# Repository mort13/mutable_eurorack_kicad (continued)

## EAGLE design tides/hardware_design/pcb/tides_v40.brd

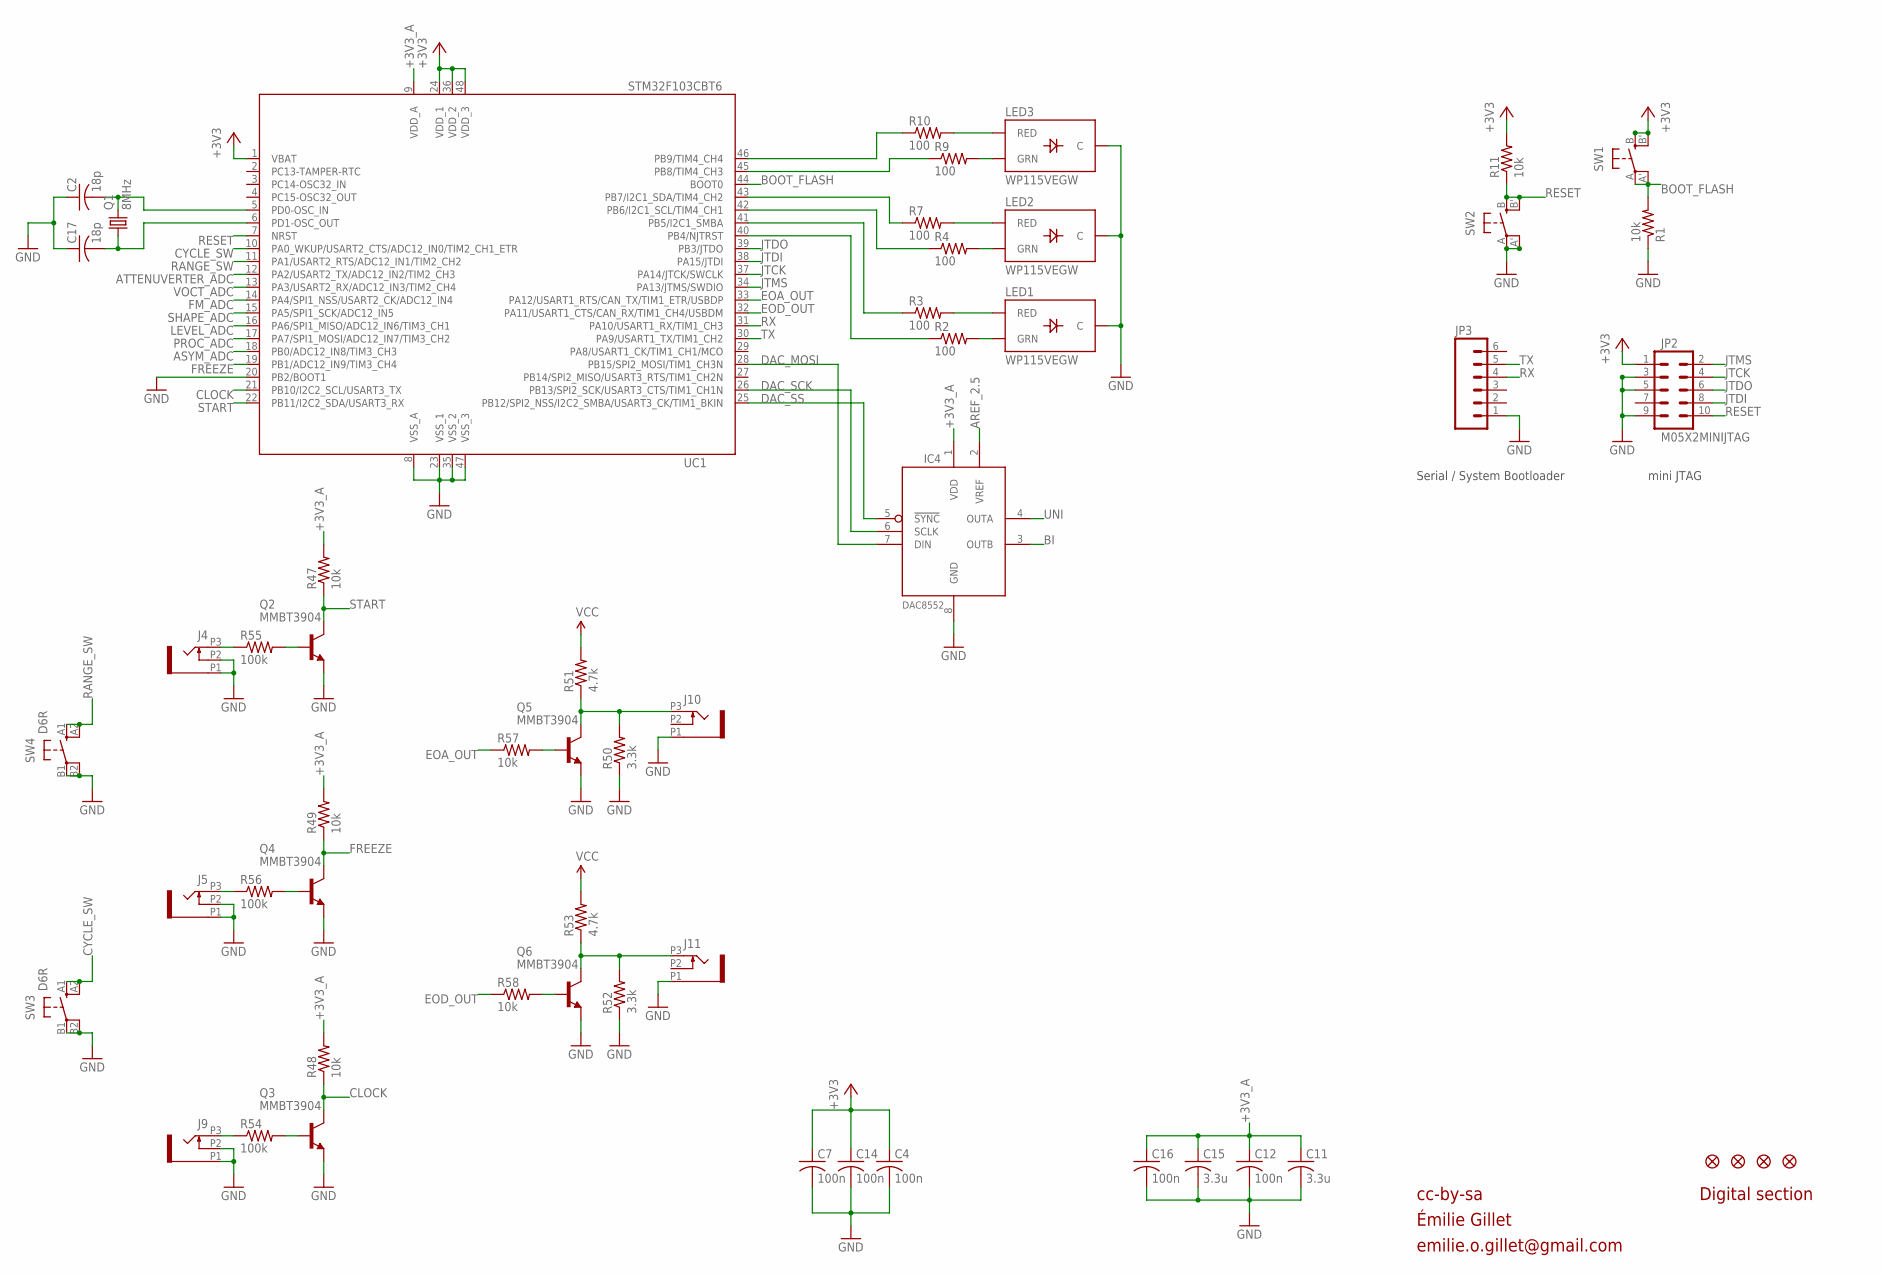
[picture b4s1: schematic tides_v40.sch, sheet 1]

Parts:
C2, C17: 18p; C0603
C4, C7, C12, C14, C16: 100n; C0603
C11, C15: 3.3u; C0603
IC4: DAC8552; MSOP-8
J4, J5, J9, J10, J11: PJ301_THONKICONN6; WQP_PJ_301M6
JP2: M05X2MINIJTAG; 2X5-1.27
JP3: M06SIP; 1X06
JP4, JP5, JP6, JP7: FIDUCIAL1X2; FIDUCIAL-1X2
LED1, LED2, LED3: WP115VEGW; LED-BICOLOR-THROUGHHOLE
Q1: 8MHz; HC49UP
Q2, Q3, Q4, Q5, Q6: MMBT3904; SOT23-BEC
R1, R11, R47, R48, R49, R57, R58: 10k; R0603
R2, R3, R4, R7, R9, R10: 100; R0603
R50, R52: 3.3k; R0603
R51, R53: 4.7k; R0603
R54, R55, R56: 100k; R0603
SW1, SW2: EVQQ2; EVQ-Q2
SW3, SW4: D6R
UC1: STM32F103CBT6; LQFP48

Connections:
+3V3: C4.1, C7.1, C14.1, JP2.1, R11.2, SW1.B (S), SW1.B' (S1), UC1.1 (VBAT), UC1.24 (VDD_1), UC1.36 (VDD_2), UC1.48 (VDD_3); also elsewhere on the board
+3V3_A: C11.1, C12.1, C15.1, C16.1, IC4.1 (VDD), R47.2, R48.2, R49.2, UC1.9 (VDD_A); also elsewhere on the board
AREF_2.5: IC4.2 (VREF); also elsewhere on the board
ASYM_ADC: UC1.18 (PB0/ADC12_IN8/TIM3_CH3); also elsewhere on the board
ATTENUVERTER_ADC: UC1.12 (PA2/USART2_TX/ADC12_IN2/TIM2_CH3); also elsewhere on the board
BI: IC4.3 (OUTB); also elsewhere on the board
BOOT_FLASH: R1.2, SW1.A, SW1.A' (P1), UC1.44 (BOOT0)
CLOCK: Q3.C, R48.1, UC1.21 (PB10/I2C2_SCL/USART3_TX)
CYCLE_SW: SW3.A1 (S), SW3.A2 (S1), UC1.10 (PA0_WKUP/USART2_CTS/ADC12_IN0/TIM2_CH1_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)
DAC_MOSI: IC4.7 (DIN), UC1.28 (PB15/SPI2_MOSI/TIM1_CH3N)
DAC_SCK: IC4.6 (SCLK), UC1.26 (PB13/SPI2_SCK/USART3_CTS/TIM1_CH1N)
DAC_SS: IC4.5 (!SYNC), UC1.25 (PB12/SPI2_NSS/I2C2_SMBA/USART3_CK/TIM1_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)
EOA_OUT: R57.1, UC1.33 (PA12/USART1_RTS/CAN_TX/TIM1_ETR/USBDP)
EOD_OUT: R58.1, UC1.32 (PA11/USART1_CTS/CAN_RX/TIM1_CH4/USBDM)
FM_ADC: UC1.14 (PA4/SPI1_NSS/USART2_CK/ADC12_IN4); also elsewhere on the board
FREEZE: Q4.C, R49.1, UC1.19 (PB1/ADC12_IN9/TIM3_CH4)
GND: C2.1, C4.2, C7.2, C11.2, C12.2, C14.2, C15.2, C16.2, C17.1, IC4.8 (GND), J4.P1 (1), J4.P2 (2), J5.P1 (1), J5.P2 (2), J9.P1 (1), J9.P2 (2), J10.P1 (1), J11.P1 (1), JP2.3, JP2.5, JP2.9, JP3.1, LED1.2 (C), LED2.2 (C), LED3.2 (C), Q2.E, Q3.E, Q4.E, Q5.E, Q6.E, R1.1, R50.1, R52.1, SW2.A, SW2.A' (P1), SW3.B1, SW3.B2 (P1), SW4.B1, SW4.B2 (P1), UC1.8 (VSS_A), UC1.20 (PB2/BOOT1), UC1.23 (VSS_1), UC1.35 (VSS_2), UC1.47 (VSS_3); also elsewhere on the board
JTCK: JP2.4, UC1.37 (PA14/JTCK/SWCLK)
JTDI: JP2.8, UC1.38 (PA15/JTDI)
JTDO: JP2.6, UC1.39 (PB3/JTDO)
JTMS: JP2.2, UC1.34 (PA13/JTMS/SWDIO)
LEVEL_ADC: UC1.16 (PA6/SPI1_MISO/ADC12_IN6/TIM3_CH1); also elsewhere on the board
unnamed: C2.2, Q1.2, UC1.5 (PD0-OSC_IN)
unnamed: C17.2, Q1.1, UC1.6 (PD1-OSC_OUT)
unnamed: J5.P3 (3), R56.1
unnamed: Q4.B, R56.2
unnamed: J9.P3 (3), R54.1
unnamed: Q3.B, R54.2
unnamed: Q6.B, R58.2
unnamed: J11.P3 (3), Q6.C, R52.2, R53.1
unnamed: LED3.3 (RED), R10.2
unnamed: LED3.1 (GRN), R9.2
unnamed: LED2.3 (RED), R7.2
unnamed: LED2.1 (GRN), R4.2
unnamed: LED1.3 (RED), R3.2
unnamed: LED1.1 (GRN), R2.2
unnamed: R10.1, UC1.46 (PB9/TIM4_CH4)
unnamed: R9.1, UC1.45 (PB8/TIM4_CH3)
unnamed: R7.1, UC1.43 (PB7/I2C1_SDA/TIM4_CH2)
unnamed: R4.1, UC1.42 (PB6/I2C1_SCL/TIM4_CH1)
unnamed: R3.1, UC1.41 (PB5/I2C1_SMBA)
unnamed: R2.1, UC1.40 (PB4/NJTRST)
unnamed: J10.P3 (3), Q5.C, R50.2, R51.1
unnamed: Q5.B, R57.2
unnamed: J4.P3 (3), R55.1
unnamed: Q2.B, R55.2
PROC_ADC: UC1.17 (PA7/SPI1_MOSI/ADC12_IN7/TIM3_CH2); also elsewhere on the board
RANGE_SW: SW4.A1 (S), SW4.A2 (S1), UC1.11 (PA1/USART2_RTS/ADC12_IN1/TIM2_CH2)
RESET: JP2.10, R11.1, SW2.B (S), SW2.B' (S1), UC1.7 (NRST)
RX: JP3.4, UC1.31 (PA10/USART1_RX/TIM1_CH3)
SHAPE_ADC: UC1.15 (PA5/SPI1_SCK/ADC12_IN5); also elsewhere on the board
START: Q2.C, R47.1, UC1.22 (PB11/I2C2_SDA/USART3_RX)
TX: JP3.5, UC1.30 (PA9/USART1_TX/TIM1_CH2)
UNI: IC4.4 (OUTA); also elsewhere on the board
VCC: R51.2, R53.2; also elsewhere on the board
VOCT_ADC: UC1.13 (PA3/USART2_RX/ADC12_IN3/TIM2_CH4); also elsewhere on the board

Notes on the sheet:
cc-by-sa
Digital section
Serial / System Bootloader
mini JTAG
Émilie Gillet
emilie.o.gillet@gmail.com

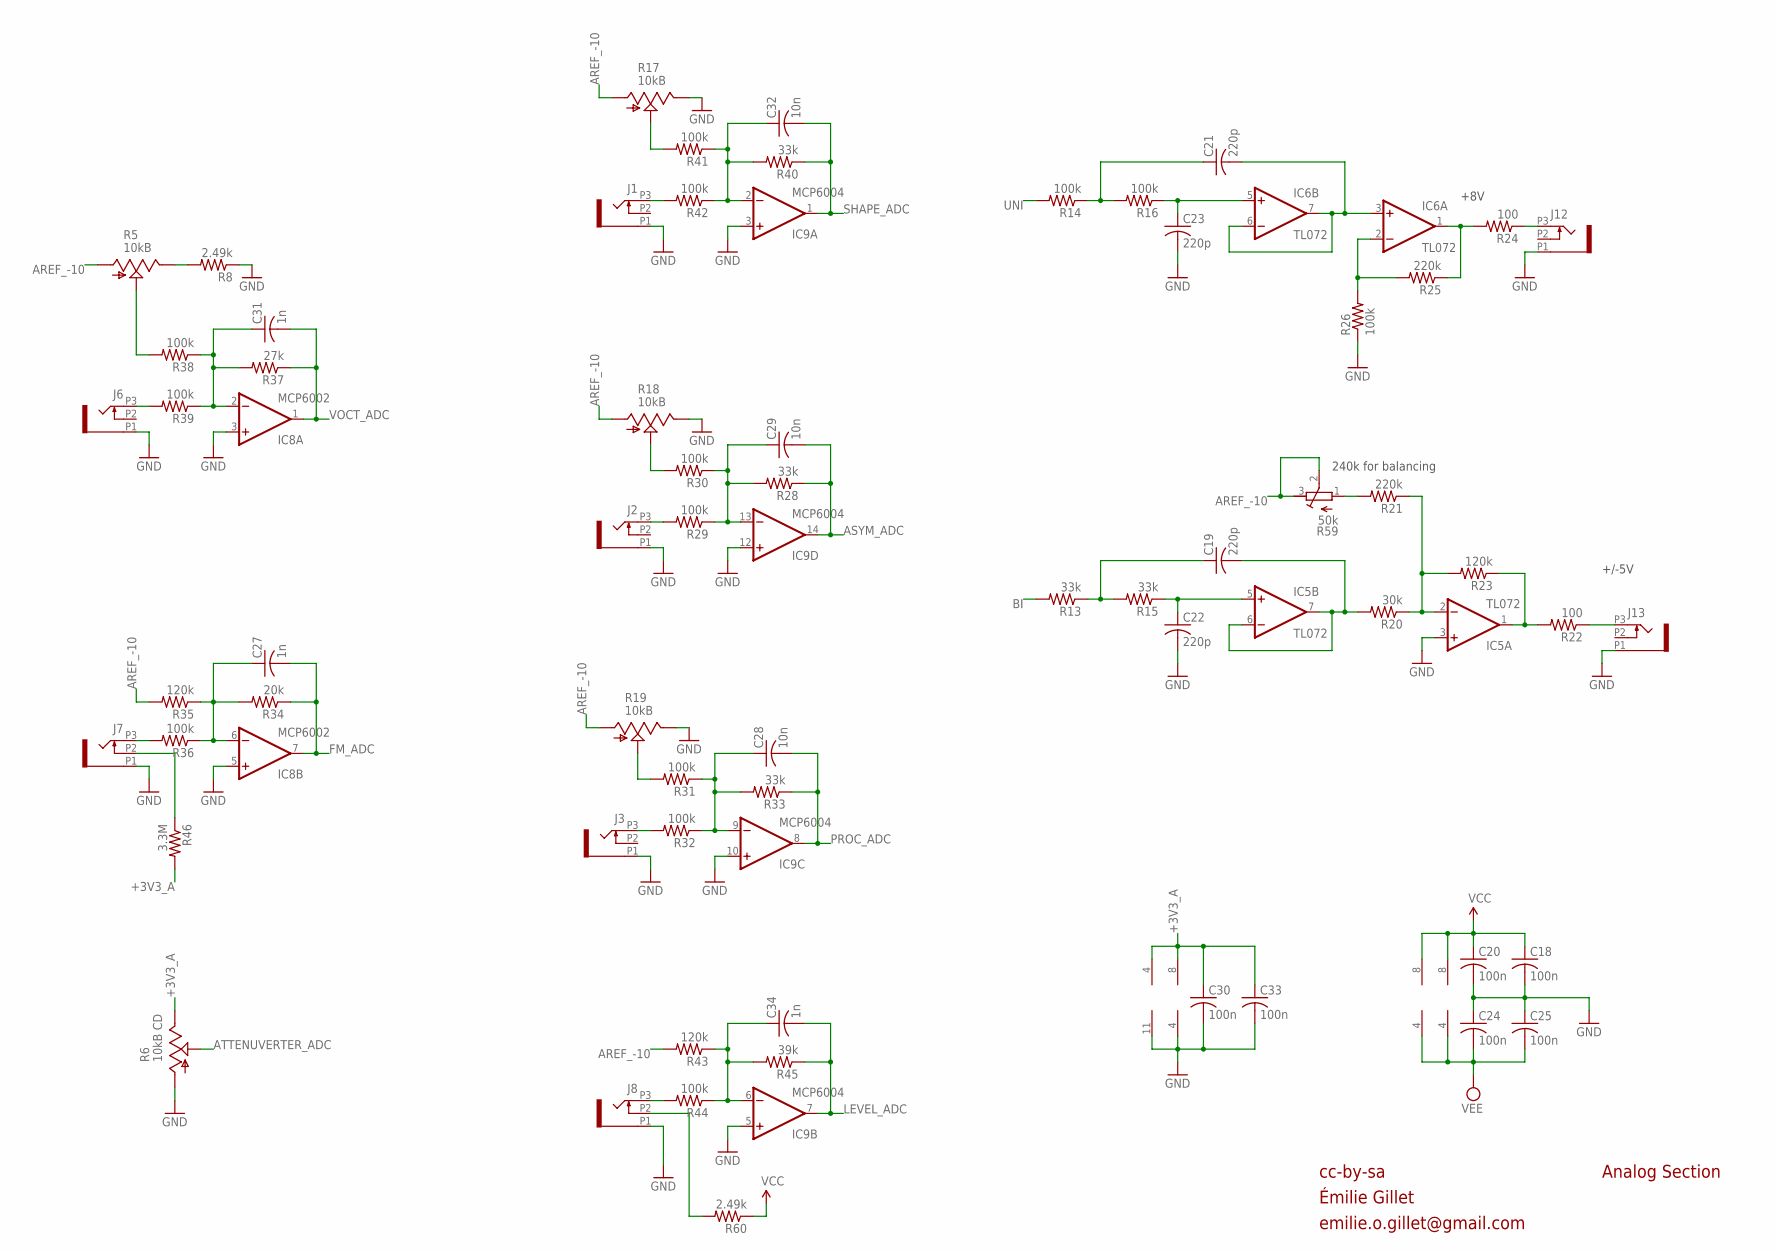
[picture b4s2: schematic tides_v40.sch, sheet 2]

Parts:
C18, C20, C24, C25, C30, C33: 100n; C0603
C19, C21, C22, C23: 220p; C0603
C27, C31, C34: 1n; C0603
C28, C29, C32: 10n; C0603
IC5, IC6: TL072; SO08
IC8: MCP6002; SO08
IC9: MCP6004; SO14
J1, J2, J3, J6, J7, J8, J12, J13: PJ301_THONKICONN6; WQP_PJ_301M6
R5, R17, R18, R19: 10kB; ALPS_POT_VERTICAL_PS
R6: 10kB CD; ALPS_POT_VERTICAL_PS
R8: 2.49k; R0603
R13, R15, R28, R33, R40: 33k; R0603
R14, R16, R26, R29, R30, R31, R32, R36, R38, R39, R41, R42, R44: 100k; R0603
R20: 30k; R0603
R21, R25: 220k; R0603
R22, R24: 100; R0603
R23, R35, R43: 120k; R0603
R34: 20k; R0603
R37: 27k; R0603
R45: 39k; R0603
R46: 3.3M; R0603
R59: 50k; RTRIM3296X
R60: 2.49k; R0805

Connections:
+3V3_A: C30.1, C33.1, IC8.8 (V+), IC9.4 (V+), R6.P$1 (E), R46.2; also elsewhere on the board
AREF_-10: R5.P$3 (A), R17.P$3 (A), R18.P$3 (A), R19.P$3 (A), R35.2, R43.2, R59.2 (S), R59.3 (A); also elsewhere on the board
ASYM_ADC: C29.2, IC9.14 (OUT), R28.1; also elsewhere on the board
ATTENUVERTER_ADC: R6.P$2 (S); also elsewhere on the board
BI: R13.2; also elsewhere on the board
BI_OUT: IC5.1 (OUT), R22.2, R23.1
FM_ADC: C27.2, IC8.7 (OUT), R34.1; also elsewhere on the board
F_CV: IC5.2 (-IN), R20.1, R21.1, R23.2
GND: C18.2, C20.2, C22.2, C23.2, C24.1, C25.1, C30.2, C33.2, IC5.3 (+IN), IC8.3 (+IN), IC8.4 (V-), IC8.5 (+IN), IC9.3 (+IN), IC9.5 (+IN), IC9.10 (+IN), IC9.11 (V-), IC9.12 (+IN), J1.P1 (1), J2.P1 (1), J3.P1 (1), J6.P1 (1), J7.P1 (1), J8.P1 (1), J12.P1 (1), J13.P1 (1), R6.P$3 (A), R8.1, R17.P$1 (E), R18.P$1 (E), R19.P$1 (E), R26.1; also elsewhere on the board
LEVEL_ADC: C34.2, IC9.7 (OUT), R45.1; also elsewhere on the board
unnamed: J1.P3 (3), R42.2
unnamed: C32.1, IC9.2 (-IN), R40.2, R41.1, R42.1
unnamed: R17.P$2 (S), R41.2
unnamed: J2.P3 (3), R29.2
unnamed: C29.1, IC9.13 (-IN), R28.2, R29.1, R30.1
unnamed: J7.P2 (2), R46.1
unnamed: R18.P$2 (S), R30.2
unnamed: J3.P3 (3), R32.2
unnamed: C28.1, IC9.9 (-IN), R31.1, R32.1, R33.2
unnamed: R19.P$2 (S), R31.2
unnamed: J8.P3 (3), R44.2
unnamed: C34.1, IC9.6 (-IN), R43.1, R44.1, R45.2
unnamed: J6.P3 (3), R39.2
unnamed: C31.1, IC8.2 (-IN), R37.2, R38.1, R39.1
unnamed: R5.P$2 (S), R38.2
unnamed: J13.P3 (3), R22.1
unnamed: R5.P$1 (E), R8.2
unnamed: J7.P3 (3), R36.2
unnamed: C27.1, IC8.6 (-IN), R34.2, R35.1, R36.1
unnamed: R21.2, R59.1 (E)
unnamed: IC6.2 (-IN), R25.2, R26.2
unnamed: C19.2, IC5.6 (-IN), IC5.7 (OUT), R20.2
unnamed: C22.1, IC5.5 (+IN), R15.1
unnamed: C19.1, R13.1, R15.2
unnamed: IC6.1 (OUT), R24.2, R25.1
unnamed: J8.P2 (2), R60.2
unnamed: C21.2, IC6.3 (+IN), IC6.6 (-IN), IC6.7 (OUT)
unnamed: C23.1, IC6.5 (+IN), R16.1
unnamed: C21.1, R14.1, R16.2
PROC_ADC: C28.2, IC9.8 (OUT), R33.1; also elsewhere on the board
SHAPE_ADC: C32.2, IC9.1 (OUT), R40.1; also elsewhere on the board
UNI: R14.2; also elsewhere on the board
UNI_OUT: J12.P3 (3), R24.1
VCC: C18.1, C20.1, IC5.8 (V+), IC6.8 (V+), R60.1; also elsewhere on the board
VEE: C24.2, C25.2, IC5.4 (V-), IC6.4 (V-); also elsewhere on the board
VOCT_ADC: C31.2, IC8.1 (OUT), R37.1; also elsewhere on the board

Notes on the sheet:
cc-by-sa
Analog Section
+8V
+/-5V
240k for balancing
Émilie Gillet
emilie.o.gillet@gmail.com

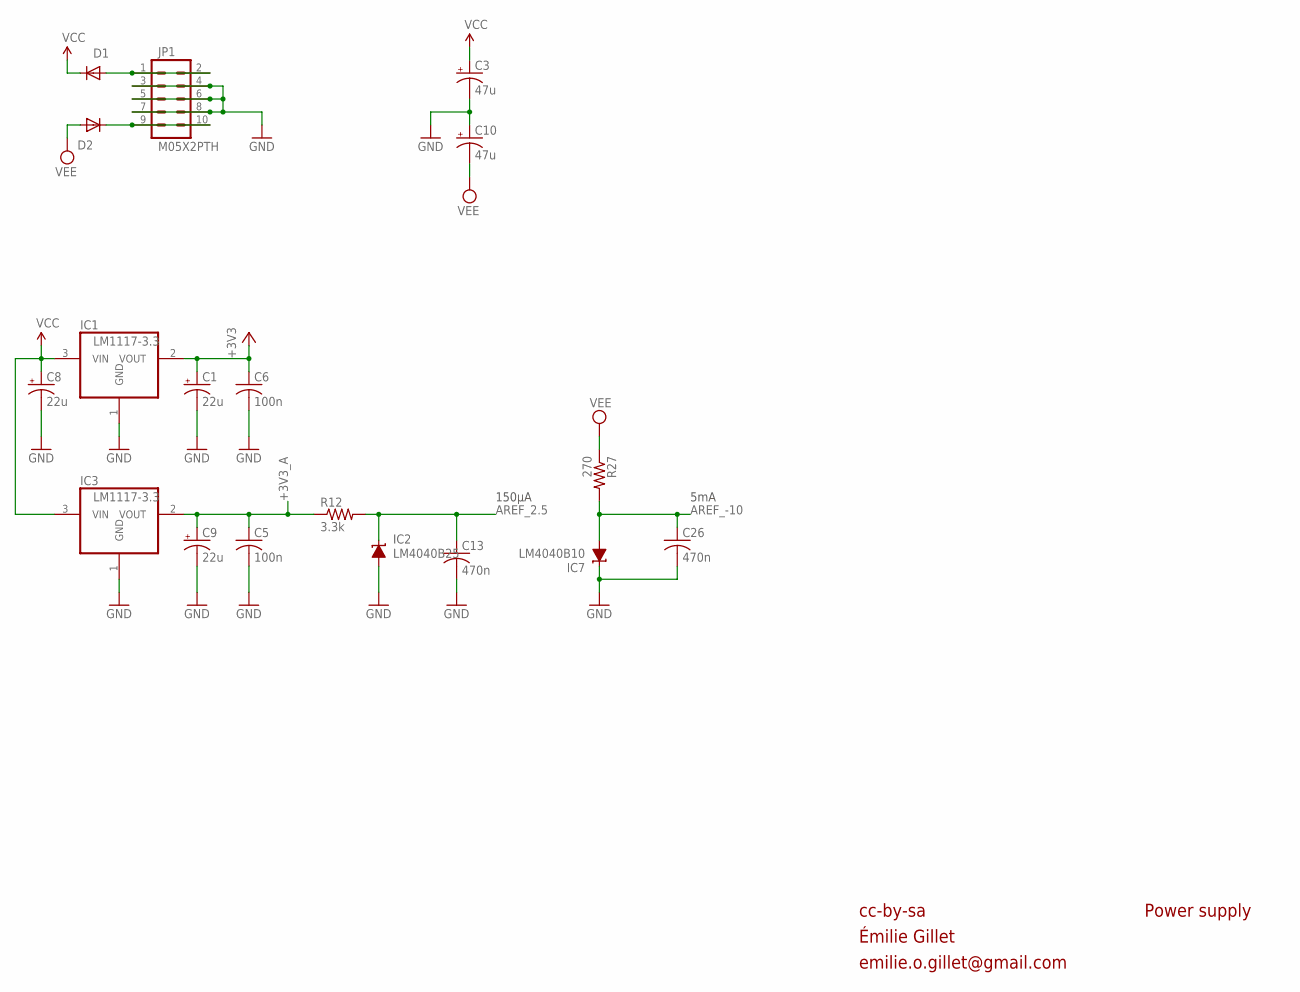
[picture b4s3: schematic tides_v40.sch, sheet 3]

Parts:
C1, C8, C9: 22u; PANASONIC_C
C3, C10: 47u; PANASONIC_D
C5, C6: 100n; C0603
C13, C26: 470n; C0603
D1, D2: 1N5819HW; SOD123
IC1, IC3: LM1117-3.3; SOT223
IC2: LM4040B25; DBZ_R-PDSO-G3
IC7: LM4040B10; DBZ_R-PDSO-G3
JP1: M05X2PTH; AVR_ICSP
R12: 3.3k; R0603
R27: 270; R0603

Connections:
+3V3: C1.+, C6.1, IC1.2 (VOUT); also elsewhere on the board
+3V3_A: C5.1, C9.+, IC3.2 (VOUT), R12.1; also elsewhere on the board
AREF_2.5: C13.1, IC2.1 (C), R12.2; also elsewhere on the board
AREF_-10: C26.1, IC7.2 (A), R27.2; also elsewhere on the board
GND: C1.-, C3.-, C5.2, C6.2, C8.-, C9.-, C10.+, C13.2, C26.2, IC1.1 (GND), IC2.2 (A), IC3.1 (GND), IC7.1 (C), JP1.3, JP1.4, JP1.5, JP1.6, JP1.7, JP1.8; also elsewhere on the board
unnamed: D1.A, JP1.1, JP1.2
unnamed: D2.C, JP1.9, JP1.10
VCC: C3.+, C8.+, D1.C, IC1.3 (VIN), IC3.3 (VIN); also elsewhere on the board
VEE: C10.-, D2.A, R27.1; also elsewhere on the board

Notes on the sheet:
cc-by-sa
Power supply
5mA
150µA
Émilie Gillet
emilie.o.gillet@gmail.com

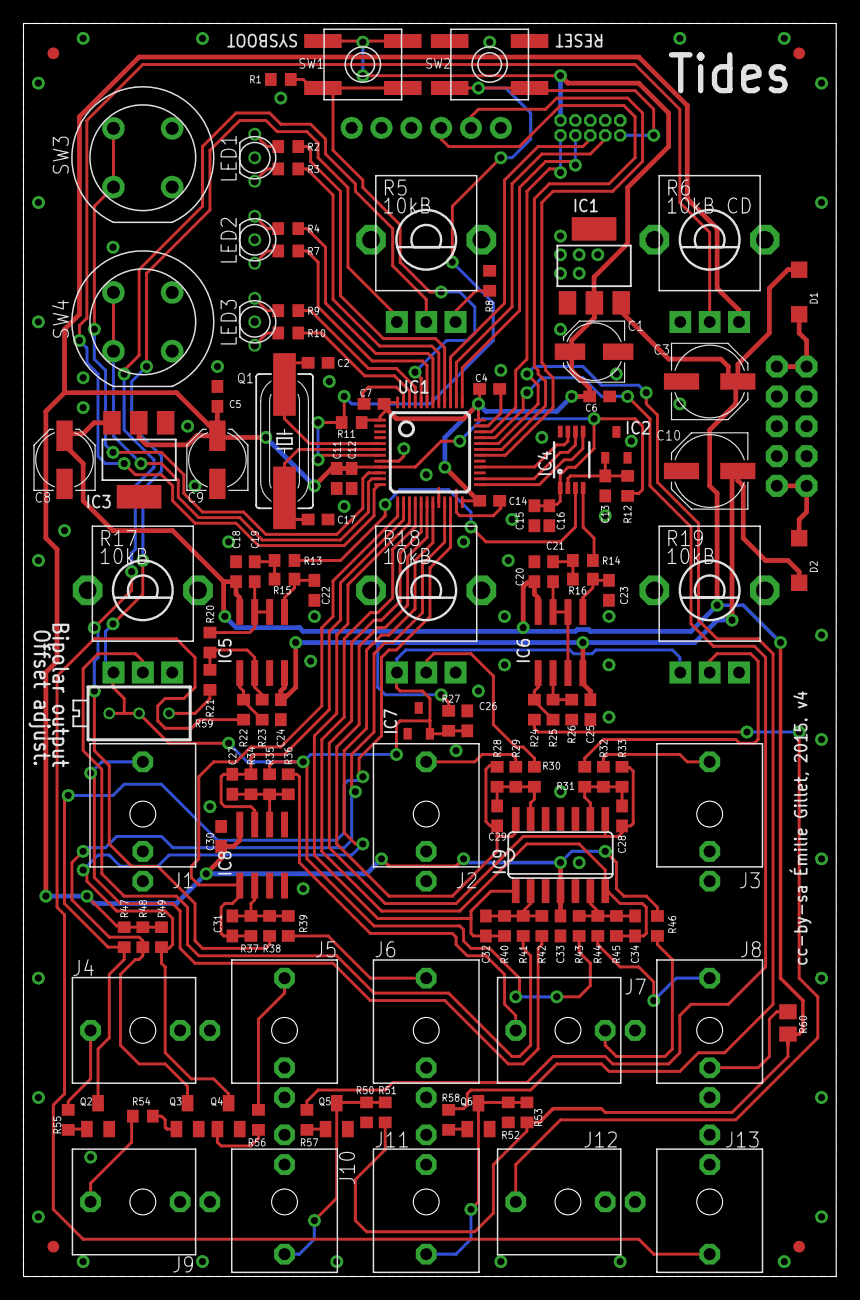
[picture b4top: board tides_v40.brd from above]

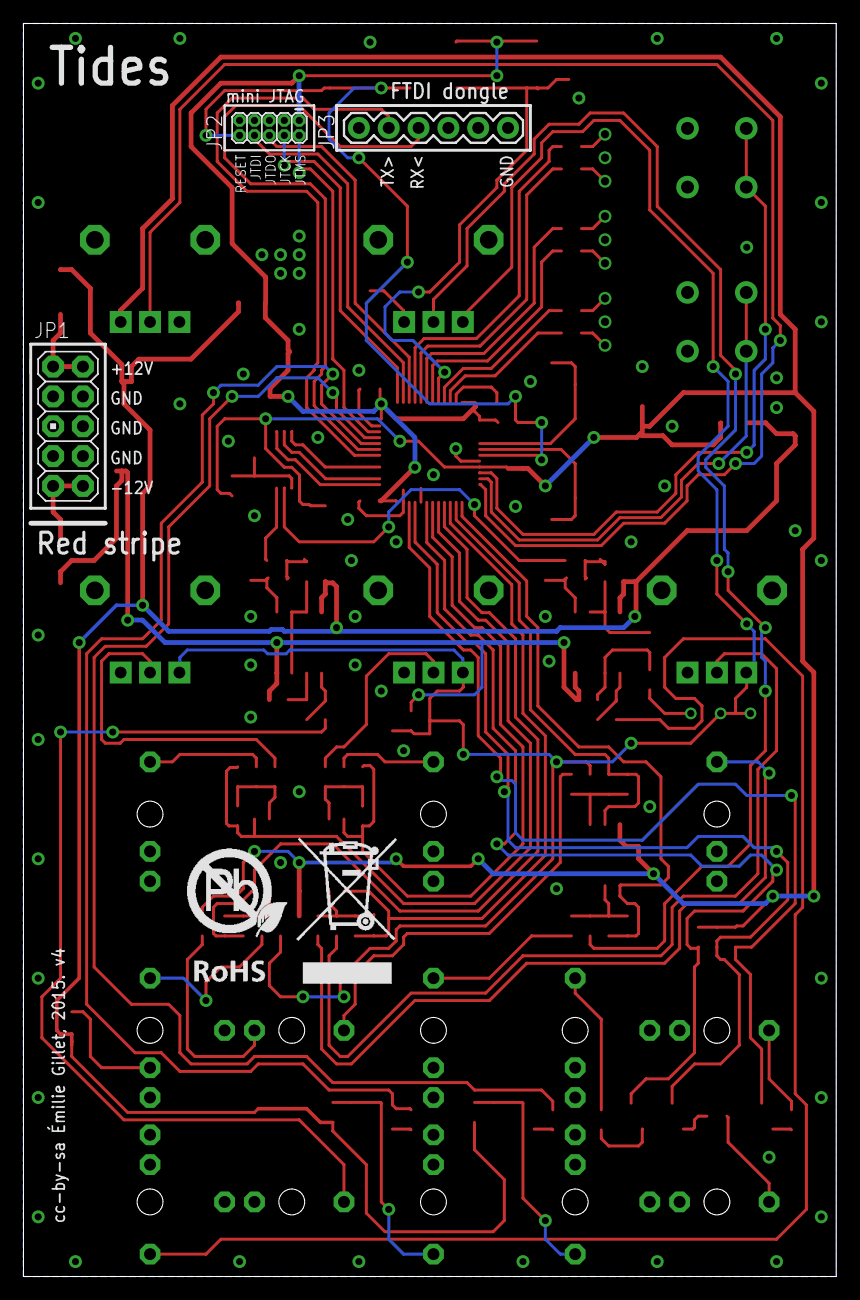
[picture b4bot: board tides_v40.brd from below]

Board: 2 copper layers, 69.2 x 106.7 mm, 140 parts (4 on the bottom side), 92 nets.

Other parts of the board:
U$3: ROHS_BIG

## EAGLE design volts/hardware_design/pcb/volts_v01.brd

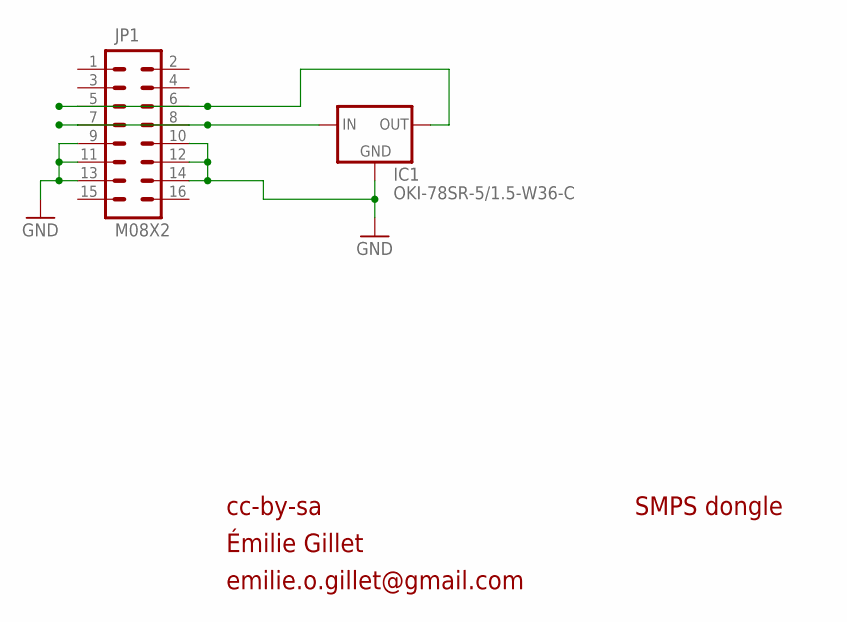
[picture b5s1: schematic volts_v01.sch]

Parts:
IC1: OKI-78SR-5/1.5-W36-C; OKI78SR
JP1: M08X2; 2X8

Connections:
GND: IC1.2 (GND), JP1.9, JP1.10, JP1.11, JP1.12, JP1.13, JP1.14
unnamed: IC1.1 (IN), JP1.7, JP1.8
unnamed: IC1.3 (OUT), JP1.5, JP1.6

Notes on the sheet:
cc-by-sa
SMPS dongle
Émilie Gillet
emilie.o.gillet@gmail.com

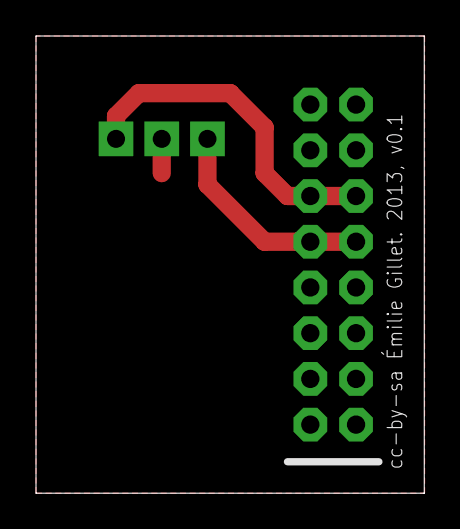
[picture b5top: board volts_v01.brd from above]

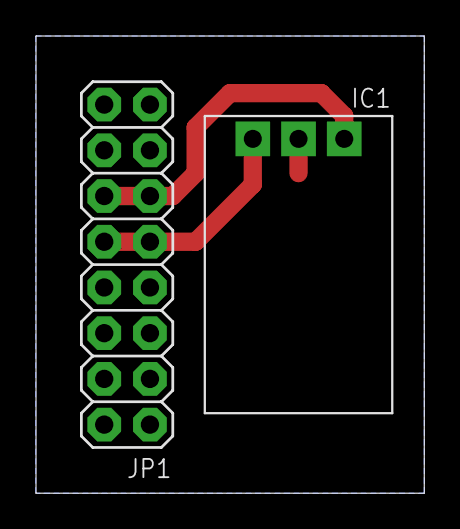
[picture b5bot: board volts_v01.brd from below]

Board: 2 copper layers, 21.6 x 25.4 mm, 4 parts (2 on the bottom side), 3 nets.

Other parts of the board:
U$1: LOGO_5VOLTS
U$2: LOGO_5VOLTS_EDIT
